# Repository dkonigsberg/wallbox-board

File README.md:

# Wallbox Interface Board

## Introduction
This repository provides the [KiCad](http://kicad-pcb.org/) project
containing the complete circuit schematic, bill-of-materials, and
PCB layout for the Wall-O-Matic Interface Board.

The interface board is a device designed to take a Seeburg Wall-O-Matic
jukebox remote, a common sight on a sterotypical 1950's diner tabletop,
and interface it to a Sonos system via Wi-Fi using an ESP8266 (ESP-12S).

The main repository for the schematics is:
https://github.com/dkonigsberg/wallbox-board

The source code for the firmware that runs on this board is here:
https://github.com/dkonigsberg/wallbox-code

A good overview of the project can be found in these blog posts:
* Part 1 - [Introduction](http://hecgeek.blogspot.com/2017/10/wall-o-matic-interface-1.html)
* Part 2 - [Procuring a Functional Wallbox](http://hecgeek.blogspot.com/2017/10/wall-o-matic-interface-2.html)
* Part 3 - [Decoding the Pulses](http://hecgeek.blogspot.com/2017/10/wall-o-matic-interface-3.html)
* Part 4 - [Inserting Coins](http://hecgeek.blogspot.com/2017/10/wall-o-matic-interface-4.html)
* Part 5 - [Designing the Circuit](http://hecgeek.blogspot.com/2017/10/wall-o-matic-interface-5.html)
* Part 6 - [Developing the Software](http://hecgeek.blogspot.com/2017/10/wall-o-matic-interface-6.html)

You can see a video about the project here:
* [Wallbox Interface Assembly and Testing](https://www.youtube.com/watch?v=2aR7-YdtxFc)

## Notes
The component libraries used in this project are a bit of a hack job, pulling
from many different sources. The KiCad cache file is included so that the
project can actually be opened without having to duplicate this.

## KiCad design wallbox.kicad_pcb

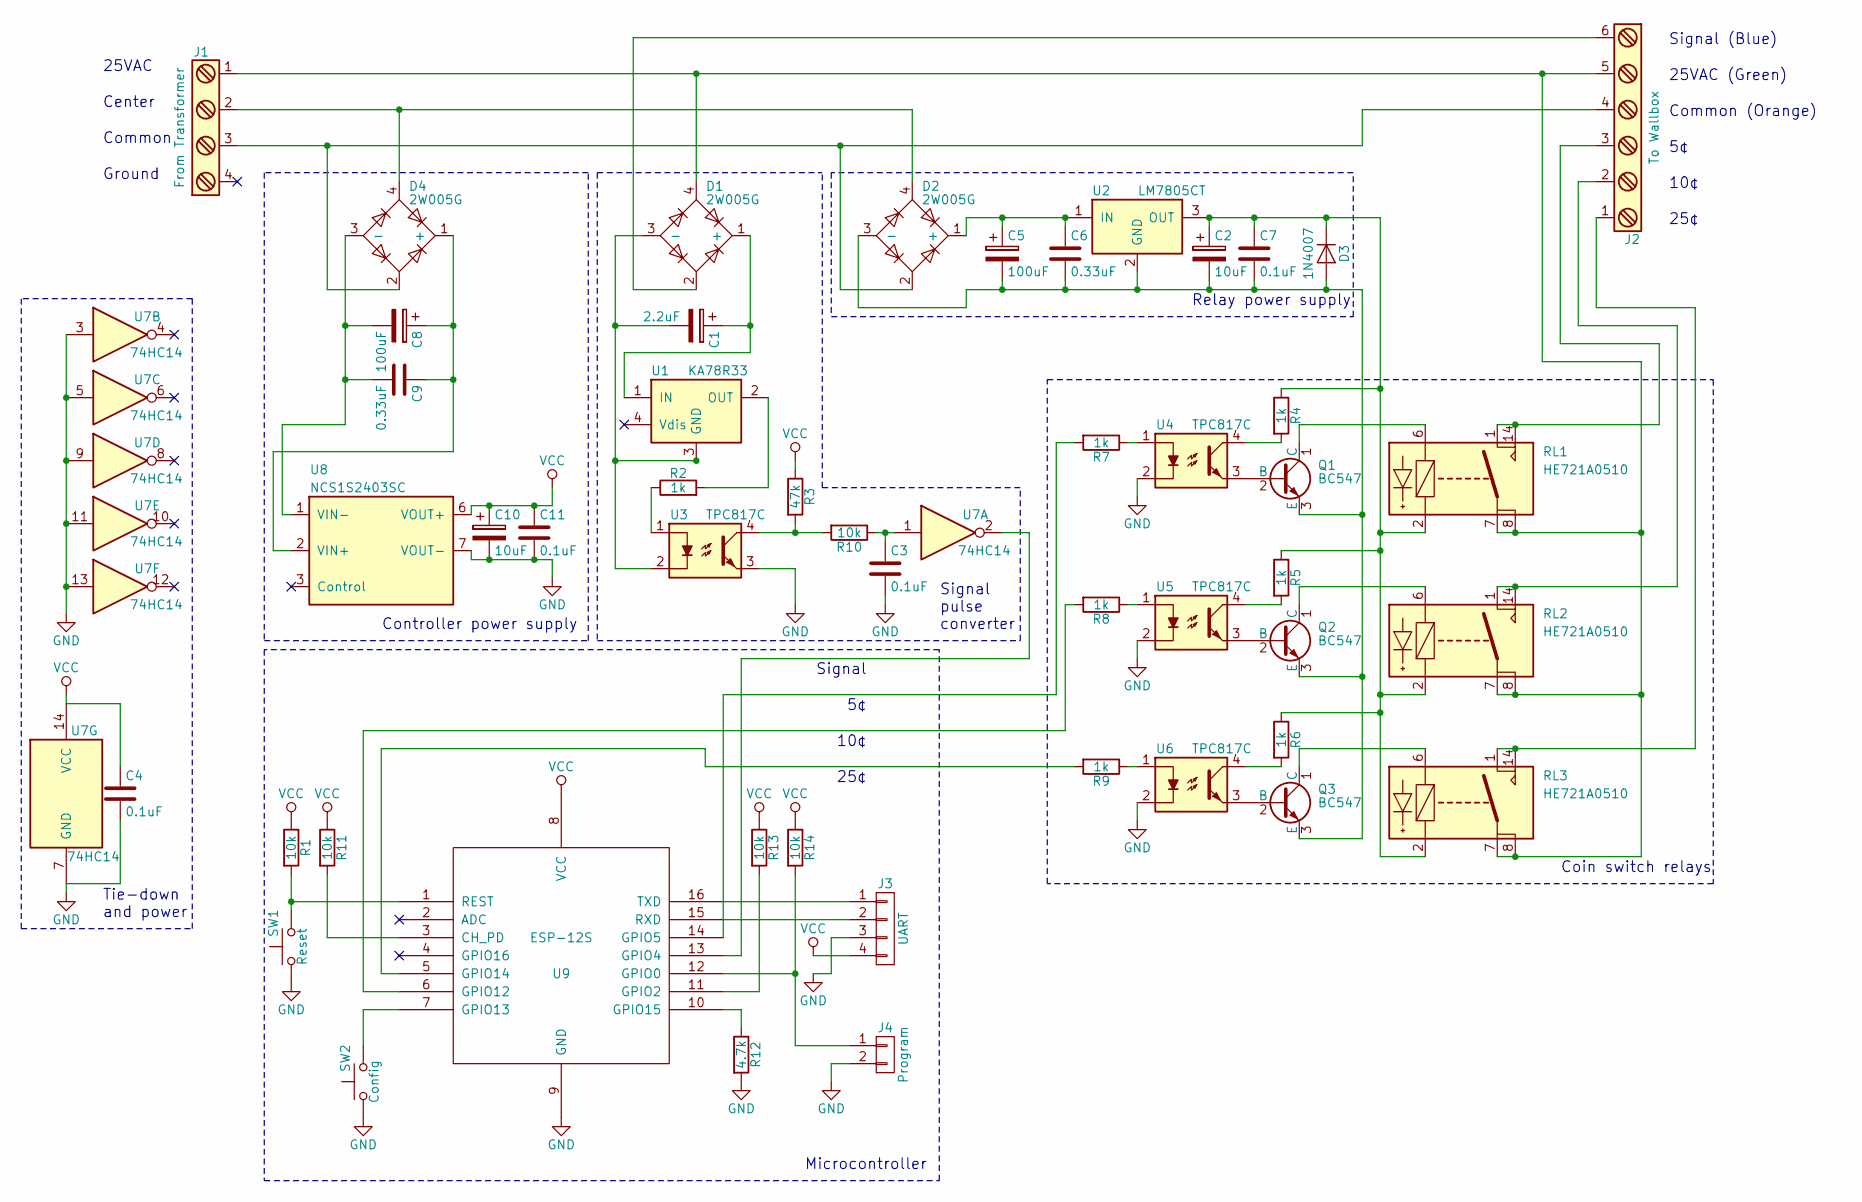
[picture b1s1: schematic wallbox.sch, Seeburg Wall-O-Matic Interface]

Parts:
C1: 2.2uF; CP_Radial_D5.0mm_P2.00mm; Manufacturer PN UPS1H2R2MDD1TD
C2, C10: 10uF; CP_Radial_D5.0mm_P2.00mm; Manufacturer PN UPW1E100MDD1TD
C3, C4, C7, C11: 0.1uF; C_Disc_D5.0mm_W2.5mm_P5.00mm; Manufacturer PN K104K15X7RF5TH5
C5, C8: 100uF; CP_Radial_D8.0mm_P3.50mm; Manufacturer PN UVZ1H101MPD1TD
C6, C9: 0.33uF; C_Disc_D6.0mm_W2.5mm_P5.00mm; Manufacturer PN KVD500L334M32A0T00
D1, D2, D4: 2W005G; D-BRIDGE-WOG; Manufacturer PN 2W005G-E4/51
D3: 1N4007; D_DO-41_SOD81_P12.70mm_Horizontal; Manufacturer PN 1N4007-TP
J1: From Transformer; TerminalBlock_Pheonix_MKDS1.5-4pol; Manufacturer PN 1729034
J2: To Wallbox; TerminalBlock_Pheonix_MKDS1.5-6pol; Manufacturer PN 1729050
J3: UART; Pin_Header_Straight_1x04_Pitch2.54mm; Manufacturer PN 61300411121
J4: Program; Pin_Header_Straight_1x02_Pitch2.54mm; Manufacturer PN 61300211121
Q1, Q2, Q3: BC547; TO-92_Molded_Narrow; Manufacturer PN BC547BBU
R1, R10, R11, R13, R14: 10k; R_Axial_DIN0207_L6.3mm_D2.5mm_P10.16mm_Horizontal; Manufacturer PN CF14JT10K0
R2, R4, R5, R6, R7, R8, R9: 1k; R_Axial_DIN0207_L6.3mm_D2.5mm_P10.16mm_Horizontal; Manufacturer PN CF14JT1K00
R3: 47k; R_Axial_DIN0207_L6.3mm_D2.5mm_P10.16mm_Horizontal; Manufacturer PN CF14JT47K0
R12: 4.7k; R_Axial_DIN0207_L6.3mm_D2.5mm_P10.16mm_Horizontal; Manufacturer PN CF14JT4K70
RL1, RL2, RL3: HE721A0510; HE700_DIP-14; Manufacturer PN HE721A0510
SW1: Reset; SW_PUSH_6mm_h5mm; Manufacturer PN 1825910-7
SW2: Config; SW_PUSH_6mm_h5mm; Manufacturer PN 1825910-6
U1: KA78R33; TO-220-4_Vertical; Manufacturer PN KA78R33CTU
U2: LM7805CT; TO-220_Vertical; Manufacturer PN LM7805CT
U3, U4, U5, U6: TPC817C; DIP-4_W7.62mm_LongPads; Manufacturer PN TPC817C C9G
U7: 74HC14; DIP-14_W7.62mm_LongPads; Manufacturer PN SN74HC14N
U8: NCS1S2403SC; DCDC-Conv_muRata_NCSxxxxSC; Manufacturer PN NCS1S2403SC
U9: ESP-12S; ESP-12S_SMD; Manufacturer PN ESP-12S

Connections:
GND: C3.2, C4.2, C10.2, C11.2, J3.3, J4.2, R12.2, SW1.1, SW2.1, U3.3, U4.2, U5.2, U6.2, U7.3, U7.5, U7.7 (GND), U7.9, U7.11, U7.13, U8.7 (VOUT-), U9.9 (GND)
unnamed: C1.1, D1.1 (+), U1.1 (IN)
unnamed: C1.2, D1.3 (-), U1.3 (GND), U3.2
unnamed: C2.1, C7.1, D3.1 (K), R4.1, R5.1, R6.1, RL1.2, RL2.2, RL3.2, U2.3 (OUT)
unnamed: C2.2, C5.2, C6.2, C7.2, D2.3 (-), D3.2 (A), Q1.3 (E), Q2.3 (E), Q3.3 (E), U2.2 (GND)
unnamed: C3.1, R10.1, U7.1
unnamed: C5.1, C6.1, D2.1 (+), U2.1 (IN)
unnamed: C8.1, C9.1, D4.1 (+), U8.2 (VIN+)
unnamed: C8.2, C9.2, D4.3 (-), U8.1 (VIN-)
unnamed: D1.2, J2.6
unnamed: D1.4, J1.1 (25VAC), J2.5, RL1.7, RL1.8, RL2.7, RL2.8, RL3.7, RL3.8
unnamed: D2.2, D4.2, J1.3 (Common), J2.4
unnamed: D2.4, D4.4, J1.2 (Center)
unnamed: J2.1, RL3.1, RL3.14
unnamed: J2.2, RL2.1, RL2.14
unnamed: J2.3, RL1.1, RL1.14
unnamed: J3.1, U9.16 (TXD)
unnamed: J3.2, U9.15 (RXD)
unnamed: J4.1, R14.2, U9.12 (GPIO0)
unnamed: Q1.1 (C), RL1.6
unnamed: Q1.2 (B), U4.3
unnamed: Q2.1 (C), RL2.6
unnamed: Q2.2 (B), U5.3
unnamed: Q3.1 (C), RL3.6
unnamed: Q3.2 (B), U6.3
unnamed: R1.2, SW1.2, U9.1 (REST)
unnamed: R2.1, U3.1
unnamed: R2.2, U1.2 (OUT)
unnamed: R4.2, U4.4
unnamed: R5.2, U5.4
unnamed: R6.2, U6.4
unnamed: R7.1, U4.1
unnamed: R7.2, U9.14 (GPIO5)
unnamed: R8.1, U5.1
unnamed: R8.2, U9.6 (GPIO12)
unnamed: R9.1, U6.1
unnamed: R9.2, U9.5 (GPIO14)
unnamed: R3.2, R10.2, U3.4
unnamed: R11.2, U9.3 (CH_PD)
unnamed: R12.1, U9.10 (GPIO15)
unnamed: R13.2, U9.11 (GPIO2)
unnamed: SW2.2, U9.7 (GPIO13)
unnamed: U7.2, U9.13 (GPIO4)
VCC: C4.1, C10.1, C11.1, J3.4, R1.1, R3.1, R11.1, R13.1, R14.1, U7.14 (VCC), U8.6 (VOUT+), U9.8 (VCC)

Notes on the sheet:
25VAC
Common
Ground
Signal (Blue)
25VAC (Green)
Common (Orange)
10¢
25¢
Signal
Center
Signal pulse converter
Relay power supply
Coin switch relays
Tie-down and power
Controller power supply
Microcontroller

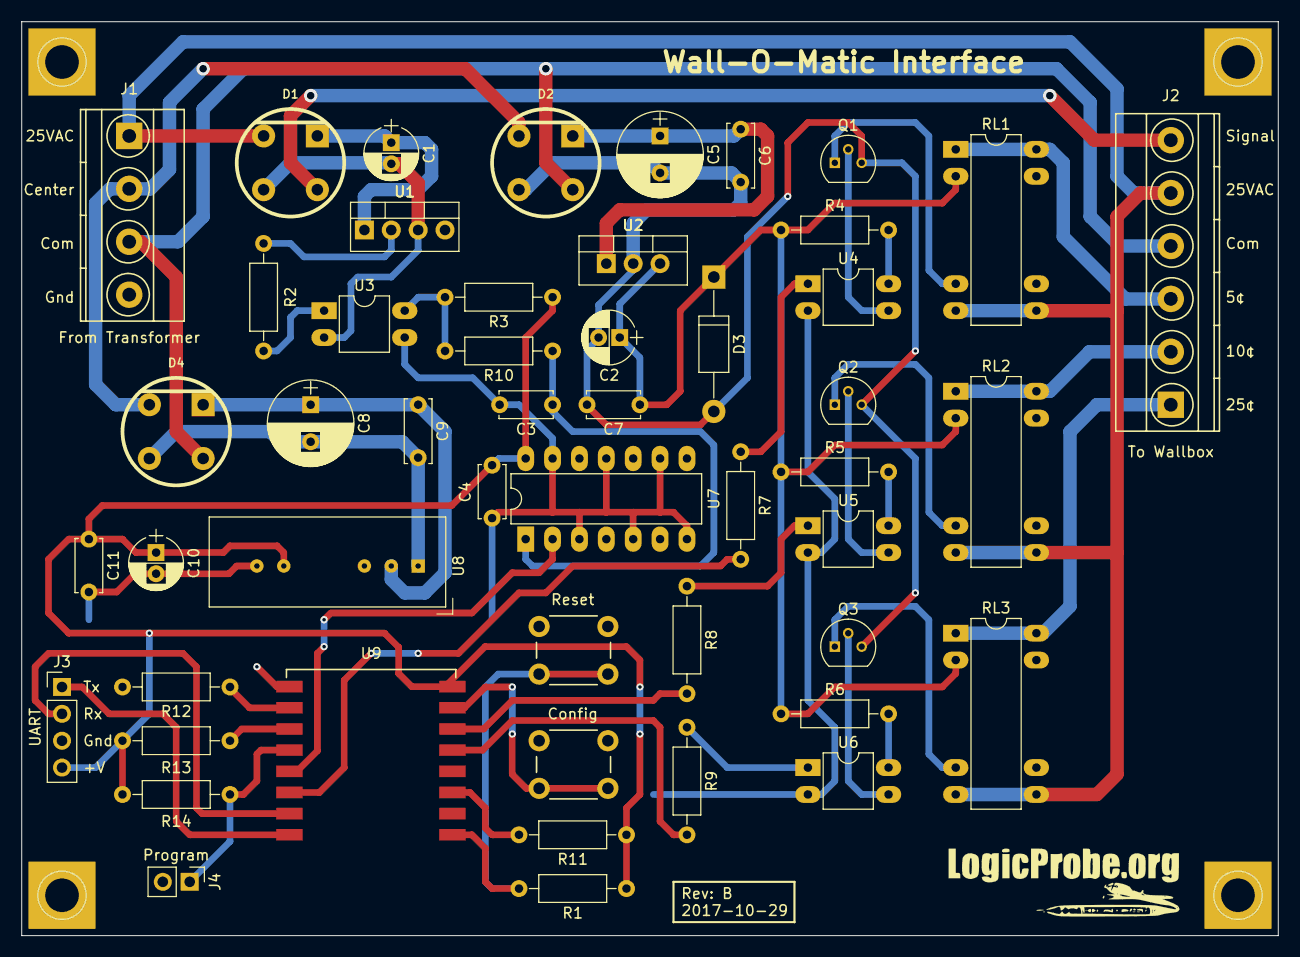
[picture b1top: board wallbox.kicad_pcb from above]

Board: 2 copper layers, 118.7 x 86.4 mm, 50 parts (0 on the bottom side), 44 nets.

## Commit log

2017-09-29 Initial empty project
2017-09-30 Initial schematic layout
2017-09-30 Initial project library files
2017-09-30 Footprint associations and imports
2017-09-30 Removed rescue library
2017-09-30 Final footprint association fixups
2017-10-02 Footprint change
2017-10-02 Component fixups and initial PCB layout
2017-10-02 Netlist file
2017-10-09 Schematic checkpointing
2017-10-09 Cloned more components into local library
2017-10-09 Schematic redraw
2017-10-09 Add block descriptions
2017-10-09 Misc tweaks
2017-10-10 Schematic component details filled in
2017-10-10 Updated capacitors, added zener, added DC-DC input components
2017-10-10 Filled in screw terminal component details
2017-10-12 Added ESP8266 to the schematic
    Hopefully the schematic is actually final now, or close to it.
2017-10-12 Respread of updated components on PCB
    Very first step of PCB layout
2017-10-12 Basic functional grouping of components
2017-10-12 Updated WOG footprint to separate label
2017-10-12 Fix WOG footprint pin numbering
2017-10-12 Routed some elements
2017-10-12 More submodules routed
2017-10-12 Getting there, just need to rearrange and route logic power
2017-10-12 More progress, added board outline
2017-10-12 Include mounting hole footprint
2017-10-12 Updated board labels
2017-10-12 Initial PCB layout complete
2017-10-13 Misc fiddling
2017-10-13 DRC updates
2017-10-13 Adding in the cache library
    This makes it easier to load the project on other computers
2017-10-13 Increase via sizes for main power traces
2017-10-13 Final markings
2017-10-16 First pass of post-rev-A fixes
    Removed Zener diode, that's probably unnecessary and wasn't working as
    intended.
    Fixed coin relay connections (25VAC instead of Common)
    Tweaked some component labels/values
2017-10-22 Fixed silkscreen labels on J3
2017-10-22 Fixed silkscreen on footprint for U8
2017-10-22 Tweaked WOG footprint for D1, D2, D4
    Slightly increased drill size to even 0.32, and increased pad size
    accordingly.
2017-10-22 Change TPC817 parts from DIP-4M version to DIP-4 version
    We could have swapped the footprints, but it makes more sense to just
    order the other size part before making another revision. That way we
    can save the DIP-4M parts for testing, and can keep the smaller
    footprint.
2017-10-26 Added controller reg caps and config button
2017-10-26 Manually updated BOM for Rev. A
2017-10-26 Initial BOM changes for Rev. B
2017-10-26 Initial routing for added components
2017-10-26 Reroute for smaller board (WIP)
2017-10-26 Opened up a 1.5in gap for condensing the components (WIP)
2017-10-27 Horizonal shrink
2017-10-27 Bottom shrink
2017-10-27 Top shrink
2017-10-27 Routing cleanup
2017-10-27 More routing cleanup work
2017-10-27 Updated WOG footprint for better hole sizes
2017-10-27 Moved all the relevant BOM data into KiCAD
2017-10-27 Refresh netlist based on BOM
2017-10-27 BOM tool config file
2017-10-29 Final markings for Rev B fabrication
2017-11-01 Added CC-BY-SA license file
2017-11-09 Added README file
2021-08-26 Add PDF of latest schematic for easy reference
